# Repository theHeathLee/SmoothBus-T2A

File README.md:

# SmoothBus T2A

An adaptation of the [SmoothBus project](https://github.com/PegorK/SmoothBus/tree/main) for the early VW bay window bus (Type 2A). Replaces the original fuel gauge mechanism with a servo-driven needle controlled by an ATTiny85 microcontroller, providing smooth movement and a low-fuel LED warning.

## Features

- Smooth servo motion — moves in 1° steps with a moving average filter (35-sample window) to eliminate sender noise
- Low-fuel LED warning when the sender reads in the reserve range
- Boot sweep sequence (empty → full → empty) to verify servo operation
- Compact PCB (~32mm × 14mm) designed to fit within the original gauge enclosure
- 3D-printable enclosure included

## How It Works

The ATTiny85 reads the fuel sender resistance via a voltage divider, applies a running average to smooth noisy readings, and drives a servo to the corresponding needle position. Calibration values are sourced from the [TheSamba forum](https://www.thesamba.com/vw/forum/viewtopic.php?t=693930) and tuned for the T2A sender:

| Sender (Ω) | Level   | Servo angle |
|-----------|---------|-------------|
| 10        | Full    | 10°         |
| 40        | Half    | 53°         |
| 55        | Quarter | 71°         |
| 70        | Reserve | 81°         |
| 79        | Empty   | 98°         |

## Repository Layout

```
SmoothBus-T2A/
├── src/SmoothBus/SmoothBus.ino   # ATTiny85 firmware (Arduino)
├── hardware/
│   ├── SmoothBusT2A.kicad_sch    # Schematic
│   ├── SmoothBusT2A.kicad_pcb    # PCB layout
│   ├── SmoothBusT2A.pdf          # Schematic PDF
│   ├── gerbers.zip               # Gerber files for PCB fabrication
│   ├── bom/ibom.html             # Interactive BOM
│   └── 3D Parts/body.stl         # 3D-printable enclosure
└── pictures/                     # Assembly and finished photos
```

## Resources

- [Interactive BOM](https://htmlpreview.github.io/?https://github.com/theHeathLee/SmoothBus-T2A/blob/main/hardware/bom/ibom.html)
- [Schematic PDF](https://github.com/theHeathLee/SmoothBus-T2A/blob/main/hardware/SmoothBusT2A.pdf)
- [Firmware README](src/README.md) — flashing instructions (Arduino Mega as ISP + ATTinyCore)

## Photos

<table>
  <tr>
    <td></td>
    <td></td>
  </tr>
  <tr>
    <td></td>
    <td></td>
  </tr>
  <tr>
    <td></td>
    <td></td>
  </tr>
</table>

## Credits

Original SmoothBus design by [Pegor Karoglanian](https://github.com/PegorK/SmoothBus/tree/main).

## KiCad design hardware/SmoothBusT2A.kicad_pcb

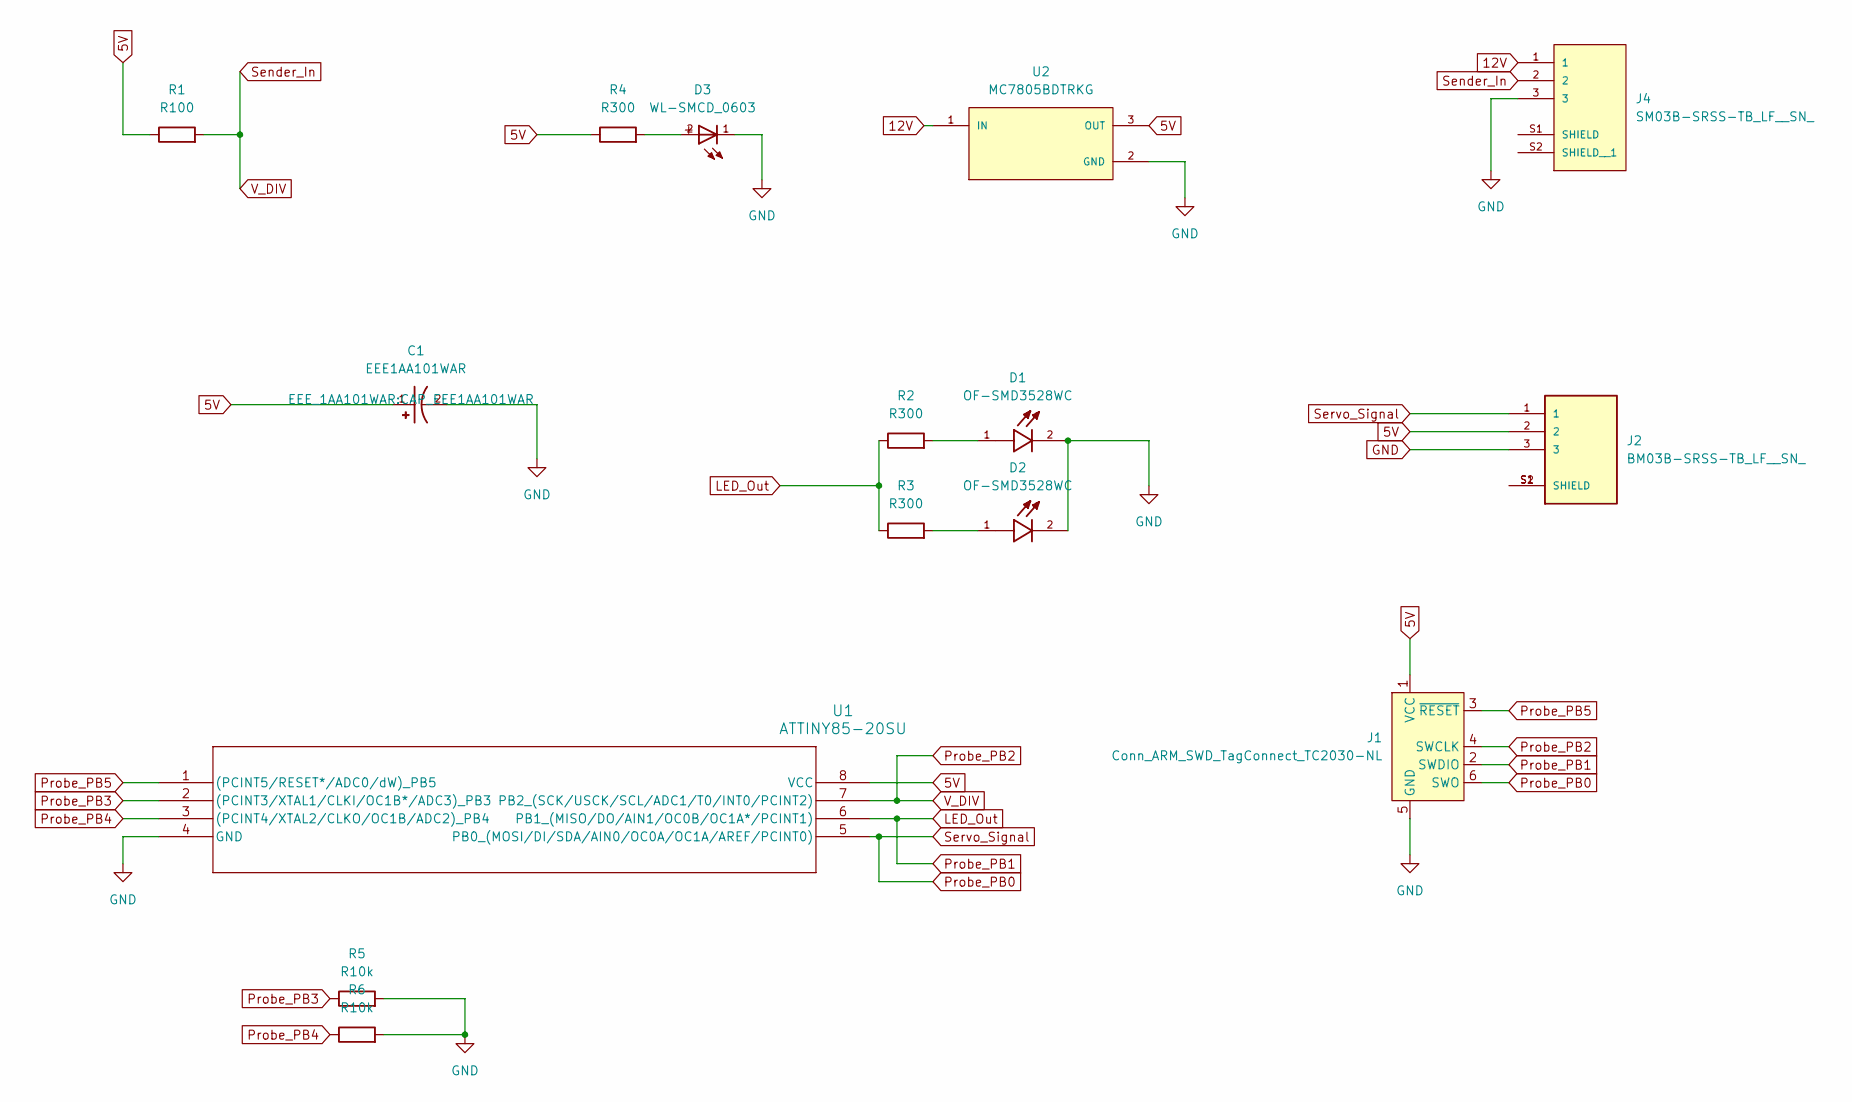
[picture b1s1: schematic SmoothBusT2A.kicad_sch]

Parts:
C1: EEE1AA101WAR; CAP_EEE1AA101WAR; PARTREV 10-Oct-19
D1, D2: OF-SMD3528WC; LED_OF-SMD3528WC; PARTREV NA
D3: WL-SMCD_0603
J1: Conn_ARM_SWD_TagConnect_TC2030-NL; Tag-Connect_TC2030-IDC-NL_2x03_P1.27mm_Vertical
J2: BM03B-SRSS-TB_LF__SN_; JST_BM03B-SRSS-TB_LF__SN_; PARTREV N/A
J4: SM03B-SRSS-TB_LF__SN_; JST_SM03B-SRSS-TB_LF__SN_
R1: R100; R_0201_0603Metric_Pad0.64x0.40mm_HandSolder
R2, R3, R4: R300; R_0201_0603Metric_Pad0.64x0.40mm_HandSolder
R5, R6: R10k; R_0201_0603Metric_Pad0.64x0.40mm_HandSolder
U1: ATTINY85-20SU; 8S2_ATM
U2: MC7805BDTRKG; DPAK229P990X238-4N; PARTREV 27

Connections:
5V: C1.1, J1.1 (VCC), J2.2, R1.1, R4.1, U1.8 (VCC), U2.3 (OUT)
12V: J4.1, U2.1 (IN)
GND: C1.2, D1.2, D2.2, D3.1, J1.5 (GND), J2.3, J4.3, R5.2, R6.2, U1.4 (GND), U2.2 (GND)
LED_Out: J1.2 (SWDIO), R2.1, R3.1, U1.6 (PB1_(MISO/DO/AIN1/OC0B/OC1A*/PCINT1))
unnamed: D1.1, R2.2
unnamed: D2.1, R3.2
unnamed: D3.2, R4.2
unnamed: J2.S1 (SHIELD), J2.S2 (SHIELD)
Probe_PB0: J1.6 (SWO), J2.1, U1.5 (PB0_(MOSI/DI/SDA/AIN0/OC0A/OC1A/AREF/PC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)
Probe_PB2: J1.4 (SWCLK), J4.2, R1.2, U1.7 (PB2_(SCK/USCK/SCL/ADC1/T0/INT0/PCINT2))
Probe_PB3: R5.1, U1.2 ((PCINT3/XTAL1/CLKI/OC1B*/ADC3)_PB3)
Probe_PB4: R6.1, U1.3 ((PCINT4/XTAL2/CLKO/OC1B/ADC2)_PB4)
Probe_PB5: J1.3 (~RESET), U1.1 ((PCINT5/RESET*/ADC0/dW)_PB5)

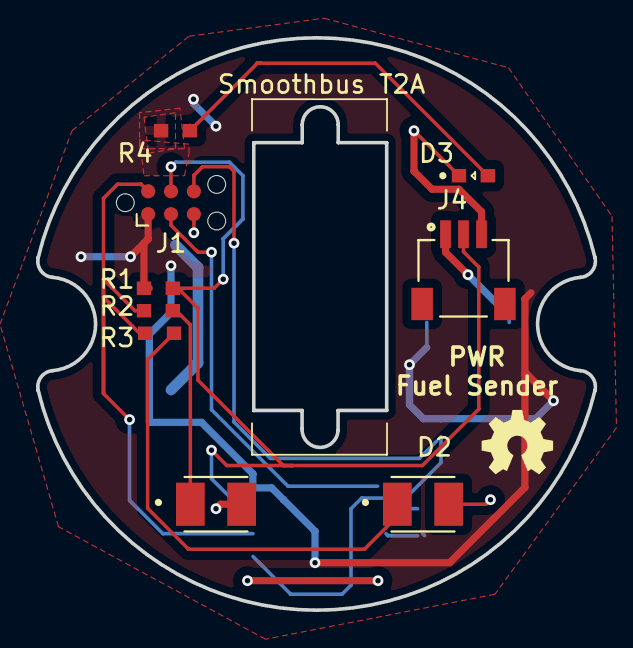
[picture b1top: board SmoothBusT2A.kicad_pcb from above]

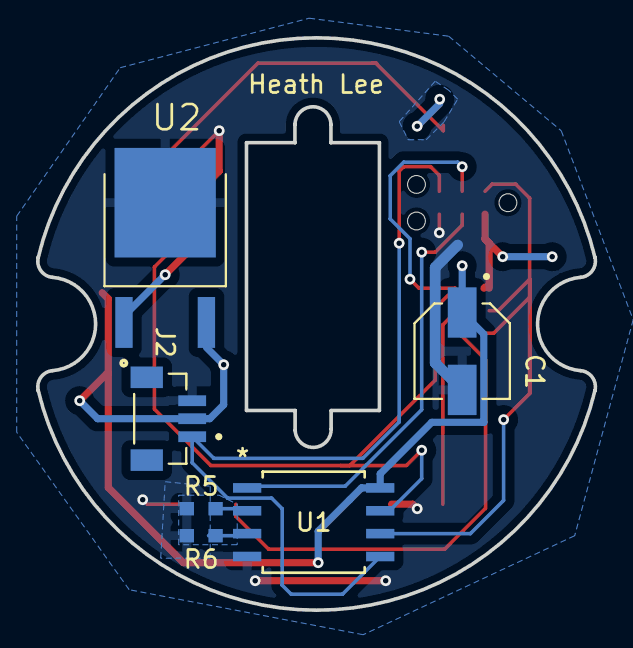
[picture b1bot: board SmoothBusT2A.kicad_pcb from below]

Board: 2 copper layers, 31.0 x 31.8 mm, 15 parts (6 on the bottom side), 13 nets.

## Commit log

2025-01-19 restructure
2025-01-28 added parts to pcb
2025-02-20 routing traces
2025-02-21 finish tracing and add bom
2025-02-21 create schematic pdf
2025-02-21 make 3d parts folder
2025-02-21 add picture
2025-02-21 render
2025-02-21 add gerbers
2025-03-08 version 1
2026-03-19 adjust values from t2b to t2a
2026-03-19 reduce servo jitter
2026-03-26 add photo
2026-03-26 Update gauge image format from PNG to JPG
2026-03-27 update reade
